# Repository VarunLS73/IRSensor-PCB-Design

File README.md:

# IRSensor
implemented PCB Design of IRSensor using KICAD Application

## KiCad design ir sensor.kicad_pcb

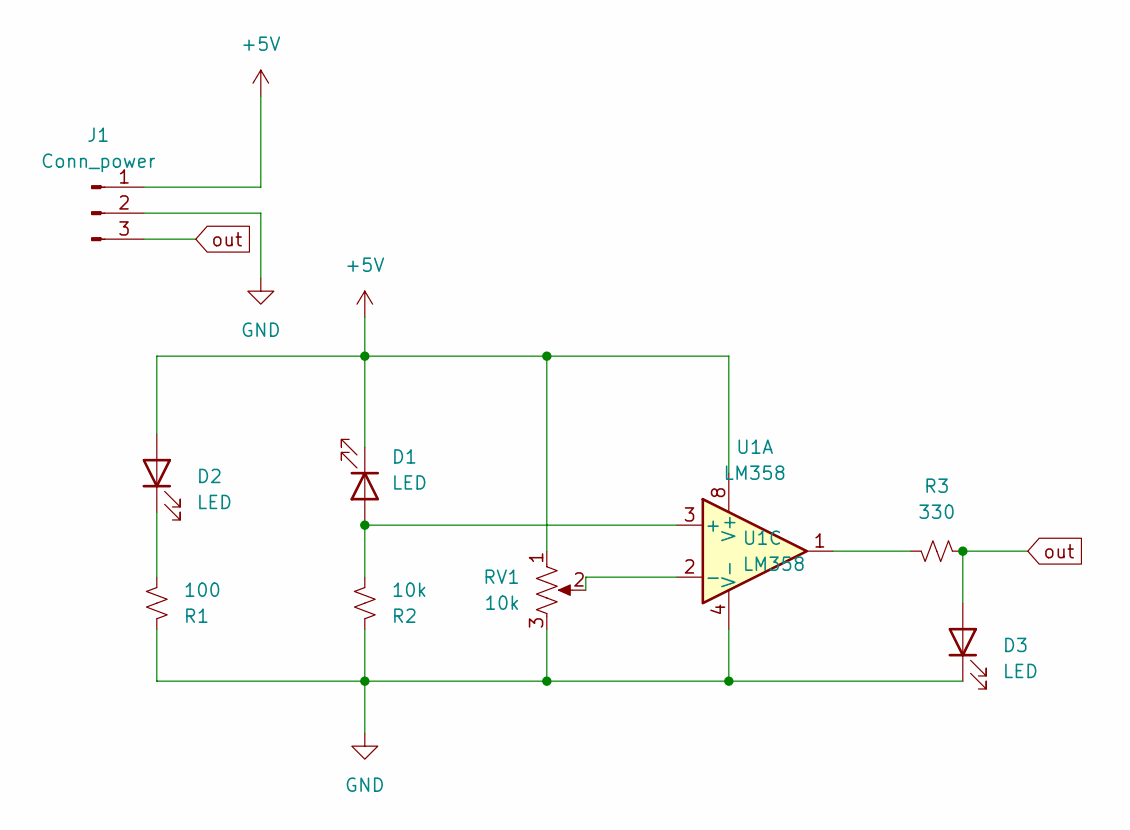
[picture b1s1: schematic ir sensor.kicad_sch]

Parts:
D1, D2: LED; LED_D5.0mm_Horizontal_O6.35mm_Z9.0mm
D3: LED; LED_1206_3216Metric_Pad1.42x1.75mm_HandSolder
J1: Conn_power; PinHeader_1x03_P2.54mm_Horizontal
R1: 100; R_1206_3216Metric
R2: 10k; R_1206_3216Metric
R3: 330; R_1206_3216Metric
RV1: 10k; Potentiometer_ACP_CA6-H2,5_Horizontal
U1: LM358; DIP-8_W7.62mm_SMDSocket_SmallPads

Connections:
+5V: D1.1 (K), D2.2 (A), J1.1, RV1.1, U1.8 (V+)
GND: D3.1 (K), J1.2, R1.1, R2.1, RV1.3, U1.4 (V-)
unnamed: D1.2 (A), R2.2, U1.3 (+)
unnamed: D2.1 (K), R1.2
unnamed: R3.2, U1.1
unnamed: RV1.2, U1.2 (-)
out: D3.2 (A), J1.3, R3.1

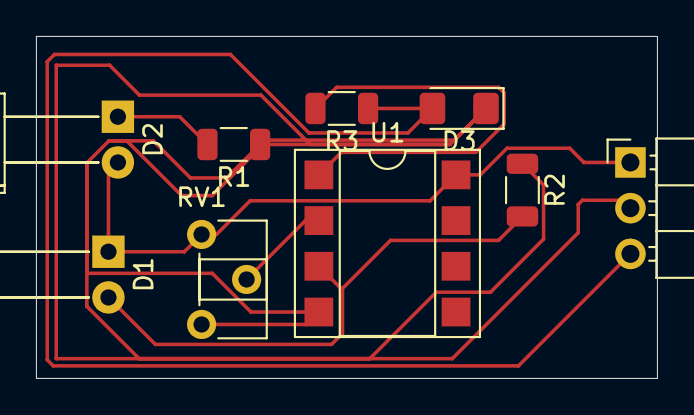
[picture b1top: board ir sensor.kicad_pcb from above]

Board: 2 copper layers, 34.5 x 19.0 mm, 9 parts (0 on the bottom side), 7 nets.
